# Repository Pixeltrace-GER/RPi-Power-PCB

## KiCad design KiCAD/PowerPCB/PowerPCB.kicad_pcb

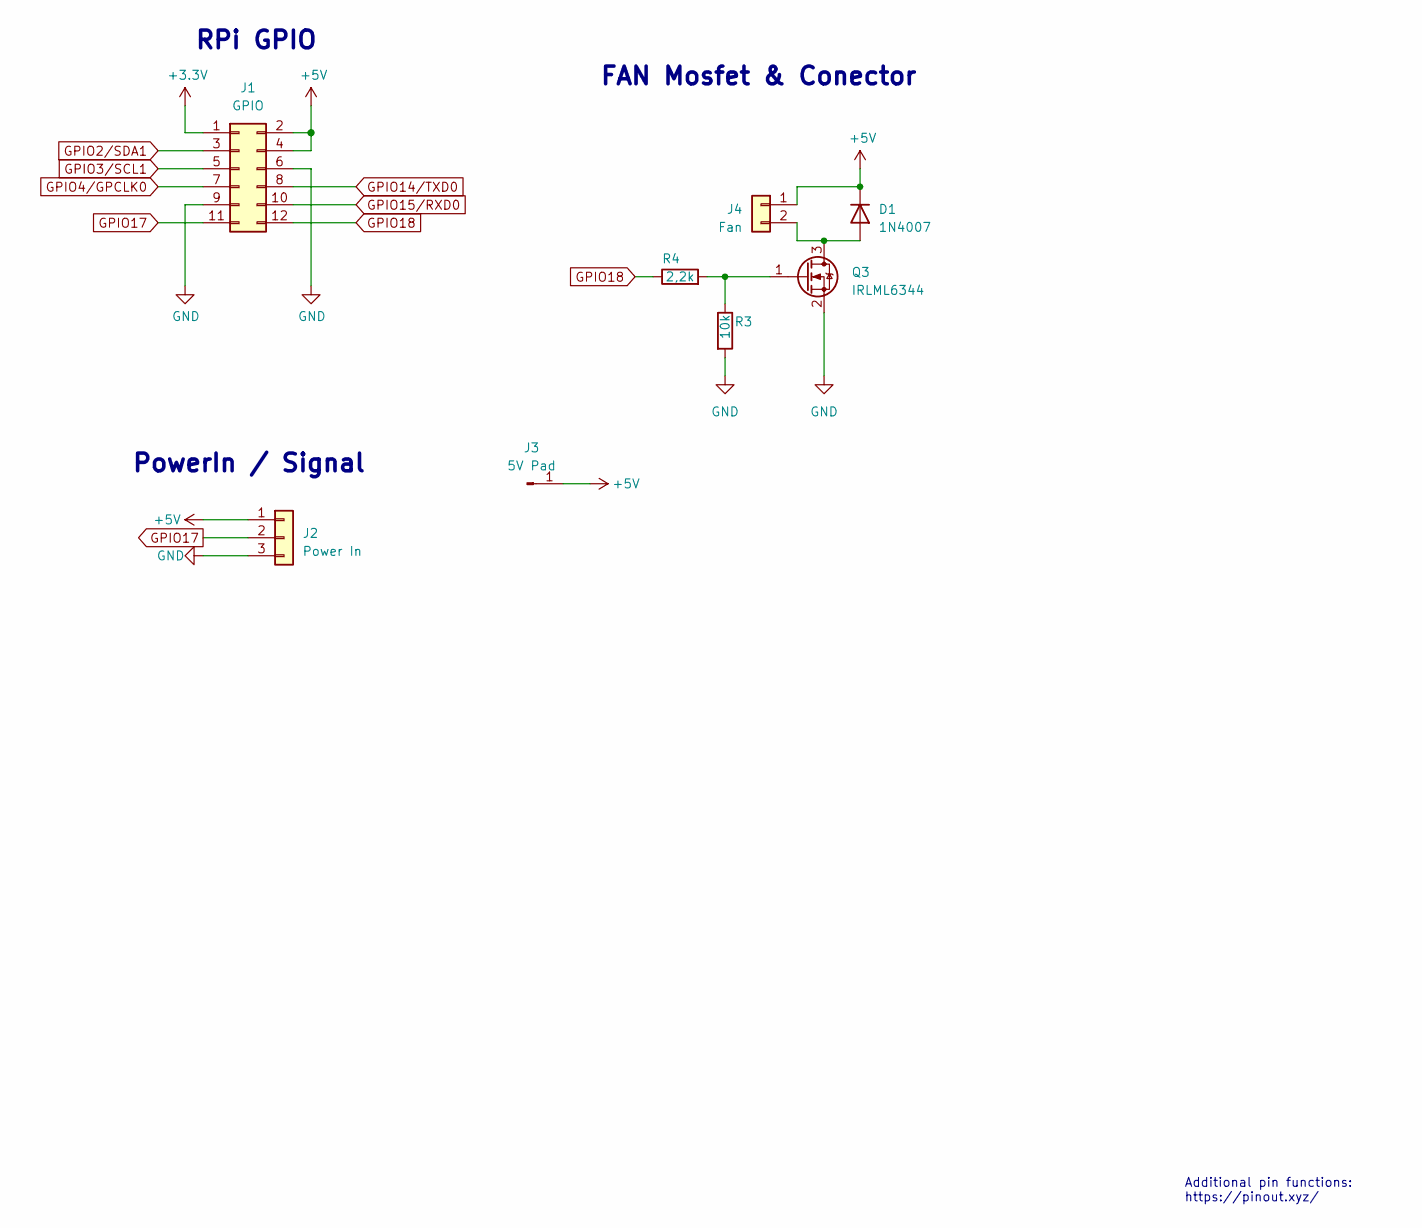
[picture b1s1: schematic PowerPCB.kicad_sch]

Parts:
D1: 1N4007; D_SOD-123F
J1: GPIO; PinSocket_2x06_P2.54mm_Vertical
J2: Power In; Molex_Micro-Fit_3.0_43650-0300_1x03_P3.00mm_Horizontal
J3: 5V Pad; TestPoint_THTPad_1.5x1.5mm_Drill0.7mm
J4: Fan; JST_XH_B2B-XH-A_1x02_P2.50mm_Vertical
Q3: IRLML6344; SOT-23
R3: 10k; R_0805_2012Metric_Pad1.20x1.40mm_HandSolder
R4: 2,2k; R_0805_2012Metric_Pad1.20x1.40mm_HandSolder

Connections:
+3V3: J1.1
+5V: D1.1 (K), J1.2, J1.4, J2.1, J3.1, J4.1
GND: J1.6, J1.9, J2.3, Q3.2 (S), R3.2
GPIO2/SDA1: J1.3
GPIO3/SCL1: J1.5
GPIO4/GPCLK0: J1.7
GPIO14/TXD0: J1.8
GPIO15/RXD0: J1.10
GPIO17: J1.11, J2.2
GPIO18: J1.12, R4.1
unnamed: D1.2 (A), J4.2, Q3.3 (D)
unnamed: Q3.1 (G), R3.1, R4.2

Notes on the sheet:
Additional pin functions: https://pinout.xyz/
FAN Mosfet & Conector
RPi GPIO
PowerIn / Signal

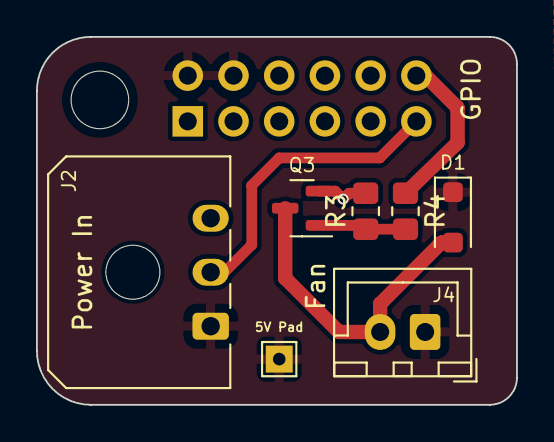
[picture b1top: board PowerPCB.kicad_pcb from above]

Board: 2 copper layers, 26.7 x 20.4 mm, 9 parts (1 on the bottom side), 6 nets.

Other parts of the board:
MH1: MountingHole_2.7mm_M2.5

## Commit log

2023-04-15 Update: Last Commit
2024-02-06 Update PCBLayout
